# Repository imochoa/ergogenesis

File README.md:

https://www.youtube.com/watch?v=X0gTMRLRNp0

# Refs
- https://docs.ergogen.xyz/
- [measure your hand](https://pashutk.com/ergopad/)
    - https://github.com/pashutk/ergopad

- flatfootfox but for my usecase:   I'd take a look at the Sweep-like example on https://ergogen.ceoloide.com/ (via the dropdown). It does the sort of direct-pin + GND setup you're looking for;

- Check out my Corney Island (https://github.com/ceoloide/corney-island), it's a 100% replica of the Corne but has support for other switches (I use Lofree switches and I am loving it)

# Similar boards
https://github.com/auryn31/avocado
https://github.com/Narkoleptika/josukey

## [Part 1: Units](https://flatfootfox.com/ergogen-part1-units-points/)
Play around on https://ergogen.ceoloide.com/

## [Part 2: Outlines](https://flatfootfox.com/ergogen-part2-outlines/)
- https://github.com/scipioni/clavis

## [Part 3: PCB](https://flatfootfox.com/ergogen-part3-pcbs/)

## [Part 4: ](https://flatfootfox.com/ergogen-part4-footprints-cases/)

https://github.com/freerouting/freerouting

# ferris reversible examples
https://github.com/davidphilipbarr/Sweep/tree/main/Sweep%20half-swept

# Routing
1. Generate `outputs/pcbs/*.kicad_pcb
2. start kicad (`pcbnew`)
    1. import `.kicad_pcb`
    2. save it to let KiCAD auto-convert the file to the newer kicad sytanx
3. `File > Export > Specctra DSN` to generate a `.dsn` file
    - save at `ergogenesis/hardware/ergogen/output/pcbs/shield-pcb.dsn`
4. Start [freerouting](https://github.com/freerouting/freerouting)
    1. run it
6. save output as a Specctra SESSION in GUI `-routed.ses`
7. from kicad, with `.kicad_pcb` from before still open...
    1. `File > Import > Specctra Session`

# 3D models

Component STEP models live in `hardware/ergogen/3dmodels/` and are wired into the
footprints in `hardware/ergogen/config.yaml` via each footprint's `*_3dmodel_filename`
params. The generated `output/pcbs/shield-pcb.kicad_pcb` references them with
the `${ERGOGEN_3DMODELS}` KiCad path variable.

Models (downloaded from github.com/Andreyod1/Axiom, the ScottoKeebs library):
- `choc_v1.step` — Kailh Choc V1 switch (PG1353)
- `choc_hotswap.step` — Choc hotswap socket
- `choc_keycap_1u.step` — MBK 1u keycap
- `supermini_nrf52840.step` — Nice!Nano V2 STEP as a SuperMini NRF52840
  stand-in (same Pro Micro form factor / USB-C; no public SuperMini STEP
  exists)
- `switch_msk12c02.step` — MSK12C02 / SSSS811101 side slide switch
- `jst_ph_s2b.step` — JST PH 2.0 side-entry battery connector (S2B-PH-K,
  from the KiCad standard library)

To make KiCad's 3D viewer resolve them, add the path variable once:
- KiCad -> Preferences -> Configure Paths... -> Add
  - Name:  `ERGOGEN_3DMODELS`
  - Value:  `<repo>/hardware/ergogen/3dmodels`

Then open `hardware/ergogen/output/pcbs/shield-pcb.kicad_pcb` -> View -> 3D Viewer.

# Cases & plates

The `cases:` section generates a sandwich case: the PCB sits between a
**stabilization (switch) plate** on top and a **base plate** on the bottom,
held together by M2 screws through the mounting holes.

- `switch_plate` / `switch_plate_ol.dxf` — top plate with Choc cutouts
  (13.8x13.8mm) at each key. The switch snaps into this plate so it can't
  fall out of the hotswap socket. 1.6mm thick (Choc clip engagement).
- `bottom_plate` / `bottom_plate_ol.dxf` — base plate with a clearance slot
  per key for the hotswap socket.

The DXFs (`output/outlines/`) are for laser/waterjet cutting the plates; the
`.jscad` cases (`output/cases/`) are 3D-printable extrusions. Convert jscad to
STL with:
```
just ergogen-stl-from-jscad
# or per file:
npx @jscad/cli@1 output/cases/switch_plate.jscad -of stla -o switch_plate.stl
```
Preview a plate outline:
```
just visualize-dxf ./output/outlines/switch_plate_ol.dxf
```

## Hotswap socket clearance (reversible board)

The Choc hotswap socket bridges the switch's central hole and a side hole on
the north side of each key. On this reversible footprint the socket sits
bottom-west when populated on the front and bottom-east when populated on the
back. Rather than generate two mirrored bases, the base uses one symmetric
12x5mm slot per key that covers **both** positions, so a single base works
for either side (and for both halves of a split where one PCB is flipped).

The slot size/position is controlled by `socket_cutout_w`, `socket_cutout_h`,
and `socket_cutout_y` in the `units:` section. If a socket fouls the base,
widening `socket_cutout_w` or raising `socket_cutout_y` gives more room.

## Notes / known gotchas

- The top-left mounting screw (`mountscrew_top_left`) sits ~2mm from the
  `pinky_top` key, so in the switch plate its hole merges into that key's
  Choc cutout. Move that screw (or the key) if you need a clean separate
  screw hole in the top plate. The base plate is unaffected.
- The case here is a bare sandwich (no walls). Walls can be added later by
  extruding an expanded outline and subtracting the board outline, à la the
  flatfootfox Part 4 case tutorial.

# ZMK
```
warning: Deprecated symbol NRF_STORE_REBOOT_TYPE_GPREGRET is enabled.
```

# Save container history

```
   0 drwxr-xr-x. 1 root   root    20 Jun  5  2024 ../
4.0K -rw-------. 1 ubuntu ubuntu 437 Nov 17 16:43 .bash_history
4.0K -rw-r--r--. 1 ubuntu ubuntu 220 Mar 31  2024 .bash_logout
4.0K -rw-r--r--. 1 root   root   475 Oct  4 14:44 .bashrc
   0 drwxr-xr-x. 5 ubuntu ubuntu  51 Nov 17 16:39 .cache/
   0 drwxr-xr-x. 3 ubuntu ubuntu  22 Nov 17 16:39 .cmake/
   0 drwxr-xr-x. 3 ubuntu ubuntu  20 Nov 17 16:30 .dotnet/
4.0K -rw-r--r--. 1 ubuntu ubuntu 760 Nov 17 16:39 .gitconfig
   0 drwx------. 2 ubuntu ubuntu  80 Nov 17 16:30 .gnupg/
   0 drwxr-xr-x. 1 root   root    17 Nov 17 15:32 .local/
4.0K -rw-r--r--. 1 ubuntu ubuntu 807 Mar 31  2024 .profile
   0 drwxr-xr-x. 2 ubuntu ubuntu  25 Nov 17 16:30 .ssh/
   0 drwxr-xr-x. 1 ubuntu ubuntu  70 Nov 17 16:30 .vscode-server/
   0 drwxr-xr-x. 1 ubuntu ubuntu   6 Nov 17 15:32 project/
```

# Reference

- https://github.com/ceoloide/corney-island
  - build in docker? https://github.com/ceoloide/corney-island/blob/main/build.sh
https://github.com/ceoloide/ergogen-footprints/tree/main

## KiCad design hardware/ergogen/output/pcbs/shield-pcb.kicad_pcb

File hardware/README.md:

# Learnings
## V1.0
- Only need to hw swap the pins that cannot be mapped via software

## V2.0
- the hotswap socket pads are long and connected to the plated holes! This makes heating them up for soldering quite hard

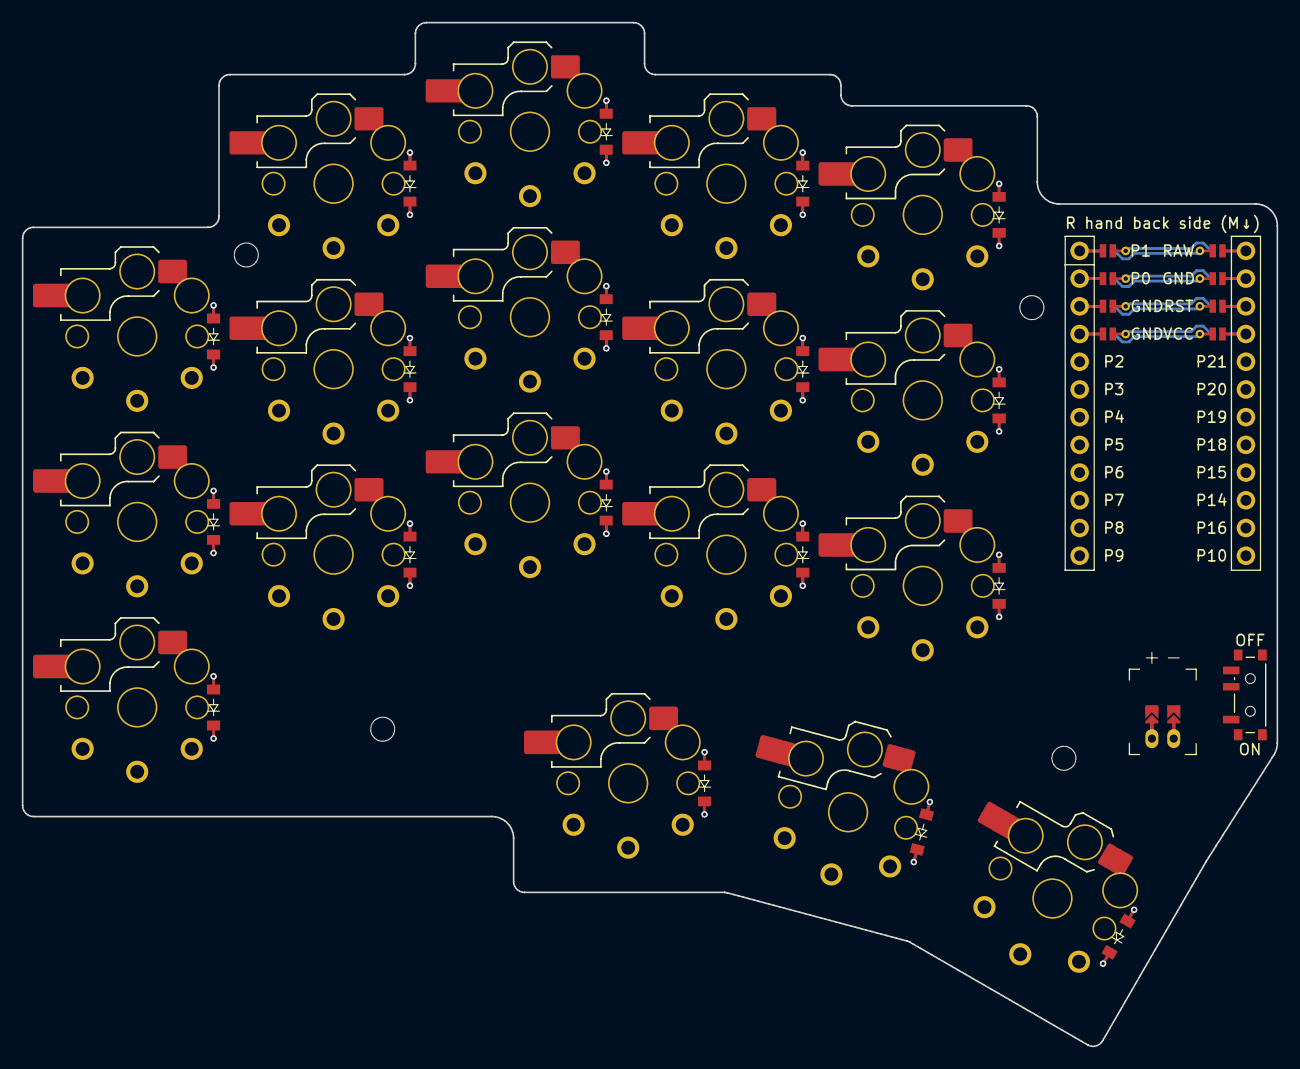
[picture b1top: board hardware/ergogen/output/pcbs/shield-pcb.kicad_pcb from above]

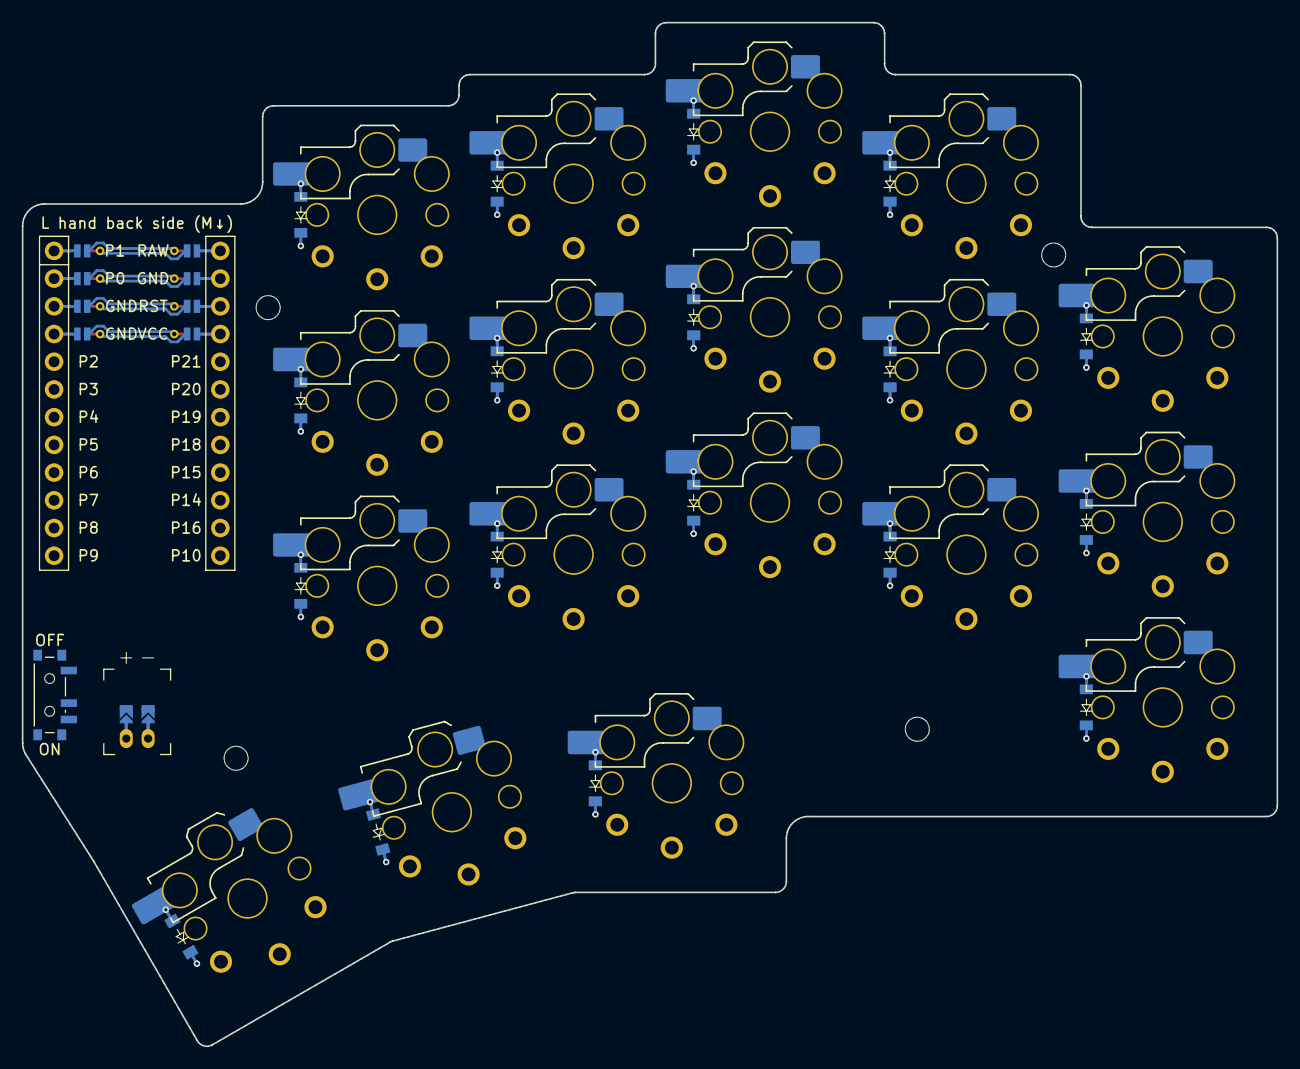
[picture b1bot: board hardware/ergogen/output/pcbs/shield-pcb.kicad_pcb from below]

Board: 2 copper layers, 115.0 x 93.8 mm, 43 parts (18 on the bottom side), 32 nets.

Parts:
D1, D2, D3, D4, D5, D6, D7, D8, D9, D10, D11, D12, D13, D14, D15, D16, D17, D18: diode_tht_sod123
JST1: battery_connector_jst_ph_2
MCU1: mcu_supermini_nrf52840
MH1, MH2, MH3, MH4: mounting_hole_npth
PWR1: power_switch_smd_side
S1, S2, S3, S4, S5, S6, S7, S8, S9, S10, S11, S12, S13, S14, S15, S16, S17, S18: switch_choc_v1_v2

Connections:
BAT_P: JST1.1, PWR1.1, PWR1.3
GND: JST1.2, MCU1.102, MCU1.121, MCU1.122
JST1_1: JST1.11, JST1.21, JST1.31
JST1_2: JST1.12, JST1.22, JST1.32
RAW: MCU1.101, PWR1.2
col0: MCU1.8, S1.1, S1.2, S2.1, S2.2, S3.1, S3.2
col1: MCU1.7, S4.1, S4.2, S5.1, S5.2, S6.1, S6.2
col2: MCU1.6, S7.1, S7.2, S8.1, S8.2, S9.1, S9.2, S16.1, S16.2
col3: MCU1.10, S10.1, S10.2, S11.1, S11.2, S12.1, S12.2, S17.1, S17.2
col4: MCU1.9, S13.1, S13.2, S14.1, S14.2, S15.1, S15.2, S18.1, S18.2
grid-zn_index_bottom: D10.2, S10.1, S10.2
grid-zn_index_home: D11.2, S11.1, S11.2
grid-zn_index_top: D12.2, S12.1, S12.2
grid-zn_inner_bottom: D13.2, S13.1, S13.2
grid-zn_inner_home: D14.2, S14.1, S14.2
grid-zn_inner_top: D15.2, S15.1, S15.2
grid-zn_middle_bottom: D7.2, S7.1, S7.2
grid-zn_middle_home: D8.2, S8.1, S8.2
grid-zn_middle_top: D9.2, S9.1, S9.2
grid-zn_pinky_bottom: D1.2, S1.1, S1.2
grid-zn_pinky_home: D2.2, S2.1, S2.2
grid-zn_pinky_top: D3.2, S3.1, S3.2
grid-zn_ring_bottom: D4.2, S4.1, S4.2
grid-zn_ring_home: D5.2, S5.1, S5.2
grid-zn_ring_top: D6.2, S6.1, S6.2
row0: D3.1, D6.1, D9.1, D12.1, D15.1, MCU1.18
row1: D2.1, D5.1, D8.1, D11.1, D14.1, MCU1.17
row2: D1.1, D4.1, D7.1, D10.1, D13.1, MCU1.16
row3: D16.1, D17.1, D18.1, MCU1.15
thumb-zn_far_thumb: D18.2, S18.1, S18.2
thumb-zn_home_thumb: D17.2, S17.1, S17.2
thumb-zn_near_thumb: D16.2, S16.1, S16.2

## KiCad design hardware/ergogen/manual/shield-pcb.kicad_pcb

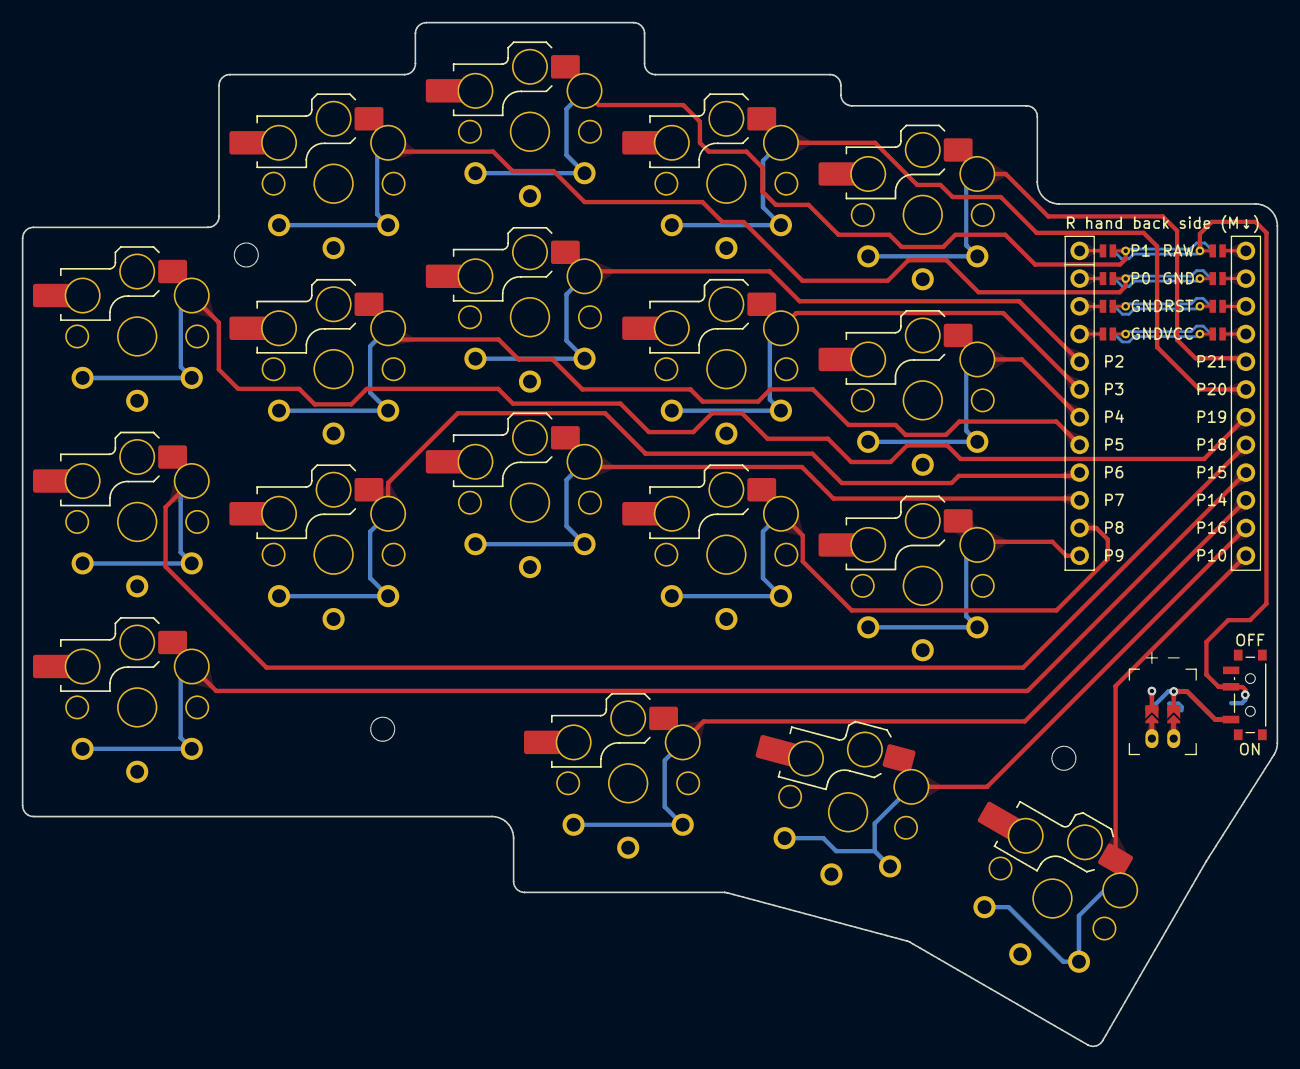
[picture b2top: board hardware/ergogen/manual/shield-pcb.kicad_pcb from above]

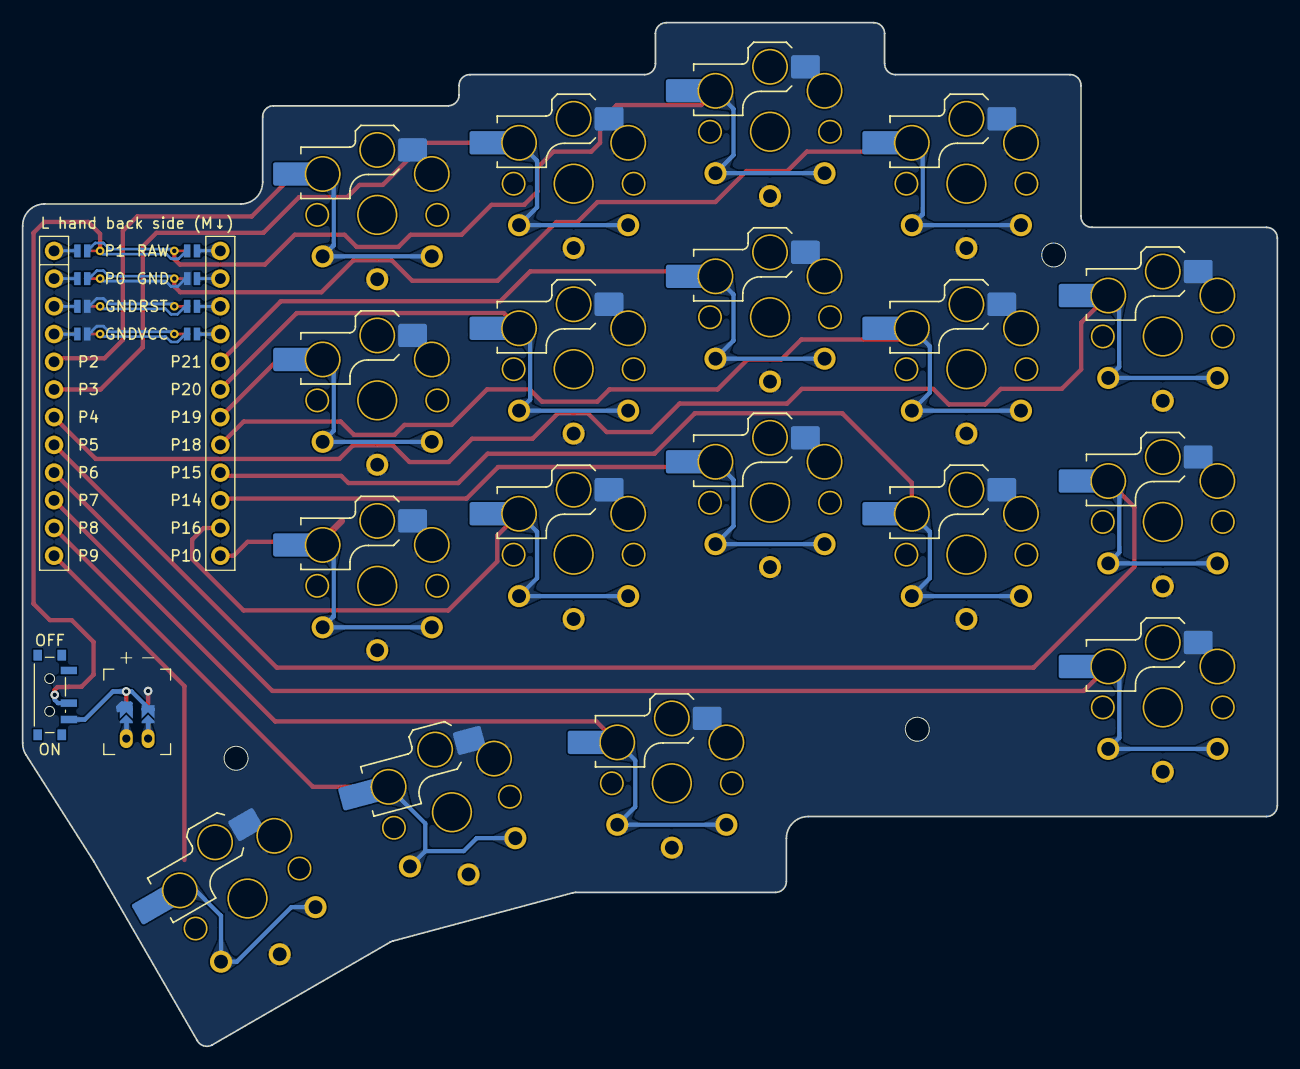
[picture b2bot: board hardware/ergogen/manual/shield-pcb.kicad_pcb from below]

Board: 2 copper layers, 115.0 x 93.8 mm, 24 parts (18 on the bottom side), 23 nets.

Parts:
JST1: battery_connector_jst_ph_2
MCU1: mcu_supermini_nrf52840
MH1, MH2, MH3: mounting_hole_npth
PWR1: power_switch_smd_side
S1, S2, S3, S4, S5, S6, S7, S8, S9, S10, S11, S12, S13, S14, S15, S16, S17, S18: switch_choc_v1_v2

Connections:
BAT_P: JST1.1, PWR1.1, PWR1.3
GND: JST1.2, MCU1.102, MCU1.121, MCU1.122, S1.1, S1.2, S2.1, S2.2, S3.1, S3.2, S4.1, S4.2, S5.1, S5.2, S6.1, S6.2, S7.1, S7.2, S8.1, S8.2, S9.1, S9.2, S10.1, S10.2, S11.1, S11.2, S12.1, S12.2, S13.1, S13.2, S14.1, S14.2, S15.1, S15.2, S16.1, S16.2, S17.1, S17.2, S18.1, S18.2
JST1_1: JST1.11, JST1.21, JST1.31
JST1_2: JST1.12, JST1.22, JST1.32
RAW: MCU1.101, PWR1.2
grid-zn_index_bottom: MCU1.14, S10.1, S10.2
grid-zn_index_home: MCU1.19, S11.1, S11.2
grid-zn_index_top: MCU1.6, S12.1, S12.2
grid-zn_inner_bottom: MCU1.13, S13.1, S13.2
grid-zn_inner_home: MCU1.18, S14.1, S14.2
grid-zn_inner_top: MCU1.5, S15.1, S15.2
grid-zn_middle_bottom: MCU1.15, S7.1, S7.2
grid-zn_middle_home: MCU1.20, S8.1, S8.2
grid-zn_middle_top: MCU1.124, S9.1, S9.2
grid-zn_pinky_bottom: MCU1.9, S1.1, S1.2
grid-zn_pinky_home: MCU1.8, S2.1, S2.2
grid-zn_pinky_top: MCU1.7, S3.1, S3.2
grid-zn_ring_bottom: MCU1.16, S4.1, S4.2
grid-zn_ring_home: MCU1.17, S5.1, S5.2
grid-zn_ring_top: MCU1.123, S6.1, S6.2
thumb-zn_far_thumb: MCU1.12, S18.1, S18.2
thumb-zn_home_thumb: MCU1.11, S17.1, S17.2
thumb-zn_near_thumb: MCU1.10, S16.1, S16.2

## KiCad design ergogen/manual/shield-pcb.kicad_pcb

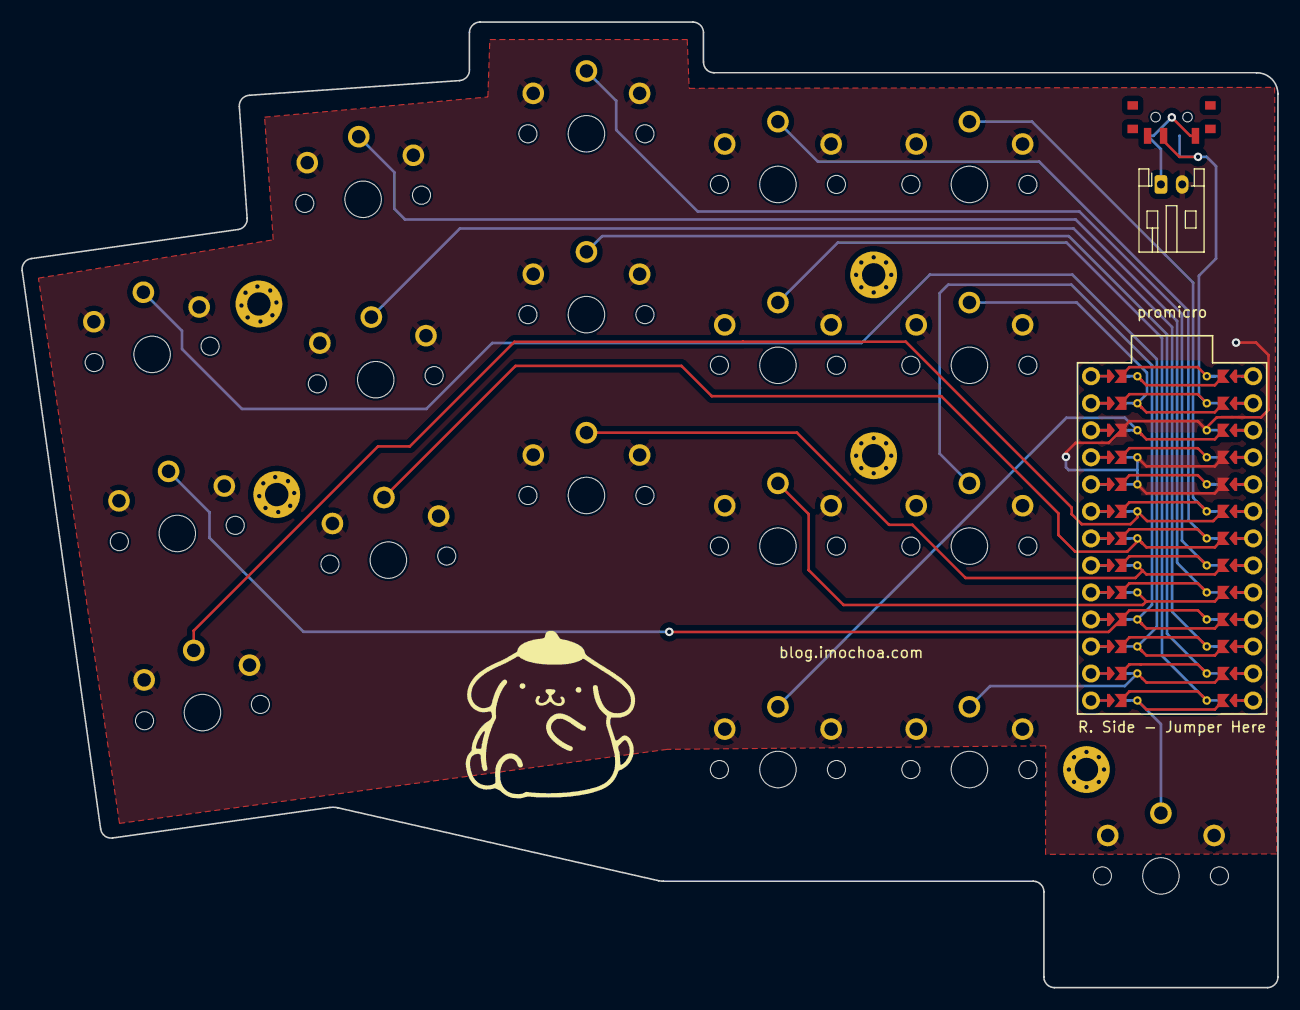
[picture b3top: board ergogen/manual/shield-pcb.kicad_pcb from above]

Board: 2 copper layers, 118.1 x 90.8 mm, 26 parts (0 on the bottom side), 21 nets.

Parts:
MCU: ProMicro
S1, S2, S3, S4, S5, S6, S7, S8, S9, S10, S11, S12, S13, S14, S15, S16, S17, S18: PG1350
T1: SW_SPDT_PCM12
_2: JST_PH_S2B-PH-K_1x02_P2.00mm_Horizontal
_6, _7, _8, _9, _10: MountingHole_2.2mm_M2_Pad_Via

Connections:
GND: MCU.3, MCU.4, MCU.23, S1.1, S2.1, S3.1, S4.1, S5.1, S6.1, S7.1, S8.1, S9.1, S10.1, S11.1, S12.1, S13.1, S14.1, S15.1, S16.1, S17.1, S18.1, _2.2
RAW: MCU.24, T1.2
grid-zn_index_bottom: MCU.8, S10.2
grid-zn_index_home: MCU.13, S11.2
grid-zn_index_top: MCU.19, S12.2
grid-zn_inner_bottom: MCU.9, S13.2
grid-zn_inner_home: MCU.1, S14.2
grid-zn_inner_top: MCU.20, S15.2
grid-zn_middle_bottom: MCU.7, S7.2
grid-zn_middle_home: MCU.14, S8.2
grid-zn_middle_top: MCU.18, S9.2
grid-zn_pinky_bottom: MCU.5, S1.2
grid-zn_pinky_home: MCU.16, S2.2
grid-zn_pinky_top: MCU.10, S3.2
grid-zn_ring_bottom: MCU.6, S4.2
grid-zn_ring_home: MCU.15, S5.2
grid-zn_ring_top: MCU.17, S6.2
pos: T1.1, _2.1
thumb-zn_far_thumb: MCU.12, S18.2
thumb-zn_home_thumb: MCU.11, S17.2
thumb-zn_near_thumb: MCU.2, S16.2

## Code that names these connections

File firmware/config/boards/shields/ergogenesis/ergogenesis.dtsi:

/*
https://github.com/zmkfirmware/zmk/blob/main/app/boards/shields/cradio/cradio.dtsi
https://github.com/auryn31/avocado/blob/main/config/boards/shields/avocado/avocado.dtsi
*/

/*
 * Copyright (c) 2020 The ZMK Contributors
 *
 * SPDX-License-Identifier: MIT
 */

#include <dt-bindings/zmk/matrix_transform.h>
#include <physical_layouts.dtsi>

// nRF52840 + Adafruit UF2 bootloader: wire up the retention "boot mode" so the
// `&bootloader` behavior can reboot into the UF2 bootloader. On Zephyr >=3.6 the
// old CONFIG_NRF_STORE_REBOOT_TYPE_GPREGRET mechanism was removed, so bootloader
// entry now goes through the retention boot-mode subsystem + magic-value mapper
// (writes 0x57 to GPREGRET). This dtsi ships with ZMK and defines the gpregret
// retention area, the zmk,bootmode-to-magic-mapper node, and the chosen nodes.
// Requires CONFIG_RETAINED_MEM/RETENTION/RETENTION_BOOT_MODE (see ergogenesis.conf).
#include <common/nordic/nrf52840_uf2_boot_mode.dtsi>

/ {
    chosen {
        zmk,kscan = &kscan0;
        zmk,physical-layout = &physical_layout0;
        zmk,battery = &vbatt;
    };

    // Each half is a 5-column x 4-row matrix. The three thumb keys occupy
    // columns 2-4 of row 3. The right half applies col-offset = <5> and this
    // transform reverses its columns to preserve the mirrored keymap order.
    default_transform: keymap_transform_0 {
        compatible = "zmk,matrix-transform";
        columns = <10>;
        rows = <4>;
        map = <
        RC(0,0) RC(0,1) RC(0,2) RC(0,3) RC(0,4)   RC(0,9) RC(0,8) RC(0,7) RC(0,6) RC(0,5)
        RC(1,0) RC(1,1) RC(1,2) RC(1,3) RC(1,4)   RC(1,9) RC(1,8) RC(1,7) RC(1,6) RC(1,5)
        RC(2,0) RC(2,1) RC(2,2) RC(2,3) RC(2,4)   RC(2,9) RC(2,8) RC(2,7) RC(2,6) RC(2,5)
                        RC(3,2) RC(3,3) RC(3,4)   RC(3,9) RC(3,8) RC(3,7)
        >;
    };

    // Custom 36-key physical layout (this is a 3+3-thumb board, so the built-in
    // 34-key cuddlykeyboards ferris layout does NOT match). Required for ZMK
    // Studio, which maps firing positions to physical keys via this node.
    //
    // key_physical_attrs: width height x y rotation rot-origin-x rot-origin-y
    // Units are 1/100 of a key. Entry order matches the keymap position order
    // in 36.h: top / home / bottom rows (L pinky->inner, R inner->pinky), then
    // left thumbs (LH2 LH1 LH0), then right thumbs (RH0 RH1 RH2). x/y are
    // approximated from the column stagger in hardware/ergogen/config.yaml
    // (pinky 0, ring +14mm, middle +4.76mm, index -4.76mm, inner -2.86mm,
    // ky=17mm) shifted positive; refine for a pixel-accurate Studio view.
    physical_layout0: physical_layout_0 {
        compatible = "zmk,physical-layout";
        display-name = "Ergogenesis";
        transform = <&default_transform>;
        kscan = <&kscan0>;

        keys  //                     w    h    x    y   rot  rx  ry
            = <&key_physical_attrs 100 100    0   82     0   0   0>
            , <&key_physical_attrs 100 100  100    0     0   0   0>
            , <&key_physical_attrs 100 100  200   54     0   0   0>
            , <&key_physical_attrs 100 100  300  110     0   0   0>
            , <&key_physical_attrs 100 100  400   99     0   0   0>
            , <&key_physical_attrs 100 100  600   99     0   0   0>
            , <&key_physical_attrs 100 100  700  110     0   0   0>
            , <&key_physical_attrs 100 100  800   54     0   0   0>
            , <&key_physical_attrs 100 100  900    0     0   0   0>
            , <&key_physical_attrs 100 100 1000   82     0   0   0>
            , <&key_physical_attrs 100 100    0  182     0   0   0>
            , <&key_physical_attrs 100 100  100  100     0   0   0>
            , <&key_physical_attrs 100 100  200  154     0   0   0>
            , <&key_physical_attrs 100 100  300  210     0   0   0>
            , <&key_physical_attrs 100 100  400  199     0   0   0>
            , <&key_physical_attrs 100 100  600  199     0   0   0>
            , <&key_physical_attrs 100 100  700  210     0   0   0>
            , <&key_physical_attrs 100 100  800  154     0   0   0>
            , <&key_physical_attrs 100 100  900  100     0   0   0>
            , <&key_physical_attrs 100 100 1000  182     0   0   0>
            , <&key_physical_attrs 100 100    0  282     0   0   0>
            , <&key_physical_attrs 100 100  100  200     0   0   0>
            , <&key_physical_attrs 100 100  200  254     0   0   0>
            , <&key_physical_attrs 100 100  300  310     0   0   0>
            , <&key_physical_attrs 100 100  400  299     0   0   0>
            , <&key_physical_attrs 100 100  600  299     0   0   0>
            , <&key_physical_attrs 100 100  700  310     0   0   0>
            , <&key_physical_attrs 100 100  800  254     0   0   0>
            , <&key_physical_attrs 100 100  900  200     0   0   0>
            , <&key_physical_attrs 100 100 1000  282     0   0   0>
            , <&key_physical_attrs 100 100  250  440     0   0   0>
            , <&key_physical_attrs 100 100  350  450     0   0   0>
            , <&key_physical_attrs 100 100  450  460     0   0   0>
            , <&key_physical_attrs 100 100  550  460     0   0   0>
            , <&key_physical_attrs 100 100  650  450     0   0   0>
            , <&key_physical_attrs 100 100  750  440     0   0   0>
            ;
    };

    kscan0: kscan {
        compatible = "zmk,kscan-gpio-matrix";
        wakeup-source;

        // Hardware path: column -> switch -> diode anode/cathode -> row.
        diode-direction = "col2row";

        // Rows are inputs for col2row scanning.
        row-gpios
            = <&pro_micro 4 (GPIO_ACTIVE_HIGH | GPIO_PULL_DOWN)> // row0: top
            , <&pro_micro 5 (GPIO_ACTIVE_HIGH | GPIO_PULL_DOWN)> // row1: home
            , <&pro_micro 6 (GPIO_ACTIVE_HIGH | GPIO_PULL_DOWN)> // row2: bottom
            , <&pro_micro 7 (GPIO_ACTIVE_HIGH | GPIO_PULL_DOWN)> // row3: thumbs
            ;

        // Columns are outputs, ordered pinky through inner.
        col-gpios
            = <&pro_micro 18 GPIO_ACTIVE_HIGH> // col0: pinky
            , <&pro_micro 19 GPIO_ACTIVE_HIGH> // col1: ring
            , <&pro_micro 20 GPIO_ACTIVE_HIGH> // col2: middle / near thumb
            , <&pro_micro 14 GPIO_ACTIVE_HIGH> // col3: index / home thumb
            , <&pro_micro 15 GPIO_ACTIVE_HIGH> // col4: inner / far thumb
            ;
    };

    // The SuperMini's onboard 1:1 battery divider uses AIN7 / P0.31, exposed
    // as Pro Micro D21. The diode matrix leaves D21 dedicated to this sensor.
    // Clone resistor values vary; calibrate these values against a multimeter.
    vbatt: vbatt {
        compatible = "zmk,battery-voltage-divider";
        io-channels = <&adc 7>;
        output-ohms = <1000000>;
        full-ohms = <2000000>;
    };
};

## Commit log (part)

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2025-08-21 1st commit
2025-08-21 pre part 1
2025-08-21 end of part1
2025-08-21 added placeholders
2025-08-26 added generation code
2025-08-26 updated inputs
2025-08-27 worked on layout
2025-09-14 extended ignores
2025-09-14 updated IDE
2025-09-14 added custom footprints
2025-09-14 updated yamls
2025-09-14 better project structure
2025-09-14 extended justfile
2025-09-14 finished the pcb generation
2025-09-14 copied sweep keyboard
2025-09-14 added comments
2025-09-14 added my updates
2025-09-14 ran fmt
2025-09-14 added discord answers
2025-09-28 set the geometry from ferris
2025-10-04 updated devcontainer
2025-10-04 added cradio config
2025-10-04 added cradio cmds
2025-10-04 added bashrc
2025-10-04 added west
2025-10-04 cleanup
2025-10-04 more ignores
2025-10-04 working cradio base
2025-10-04 updated ignores
2025-10-04 updated dtsi to be for 36 keys!
2025-10-04 test layout
2025-10-04 added warning
2025-10-06 added near thumb config
2025-10-06 added firmware dir
2025-10-12 added text and image
2025-10-13 minor updates
2025-10-15 worked on config
2025-10-16 definitive
2025-10-16 pushign
2025-10-18 status
2025-10-19 ordered
2025-10-19 added 3D models
2025-10-19 added images
2025-11-16 catching up
2025-11-16 pushed status quo
2025-11-16 added just modules
2025-11-16 added minor updates
2025-11-16 fixed spelling mistake
2025-11-16 working config
2025-11-16 fixed the custom board structure
2025-11-17 fixed scripts
2025-11-17 working build
2025-11-17 cleaned zmk config
2025-11-17 cleaned up justfile
2025-11-17 added recipes to run in devc
2025-11-17 building in devc
2025-12-09 copied over project
2025-12-10 fixed key position
2026-02-07 added yaml schema
2026-02-07 fixed padding
2026-02-07 fixed mcu part
2026-02-07 added mirroring
2026-02-08 added ergogen-footprints submodule
2026-02-08 updated nix
2026-02-08 basic devcontainer
2026-02-08 status quo
2026-02-08 cleaned up reversible board
2026-02-08 big improvements
2026-02-09 swapped the pcb footprints
2026-02-10 moved my footprints
2026-02-10 added better structure
2026-06-27 reconsidering
2026-06-27 added filled zone
2026-06-27 fixed weird space between columns
2026-06-28 looking ok
